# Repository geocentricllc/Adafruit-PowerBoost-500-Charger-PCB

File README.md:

This design is derived from Adafruit's PowerBoost-500 Charger PCB (See attribution below).  The design removes the breakout headers and changes the
USB female connector to a JST M2 right angle connector.

Adafruit-PowerBoost-500-Charger-PCB
=================================

PCB files for the Adafruit PowerBoost 500 Charger

Pick up one today at 

----> https://www.adafruit.com/product/1944

Adafruit invests time and resources providing this open source design, 
please support Adafruit and open-source hardware by purchasing 
products from Adafruit!

Designed by Adafruit Industries.  
Creative Commons Attribution, Share-Alike license, check license.txt for more information
All text above must be included in any redistribution

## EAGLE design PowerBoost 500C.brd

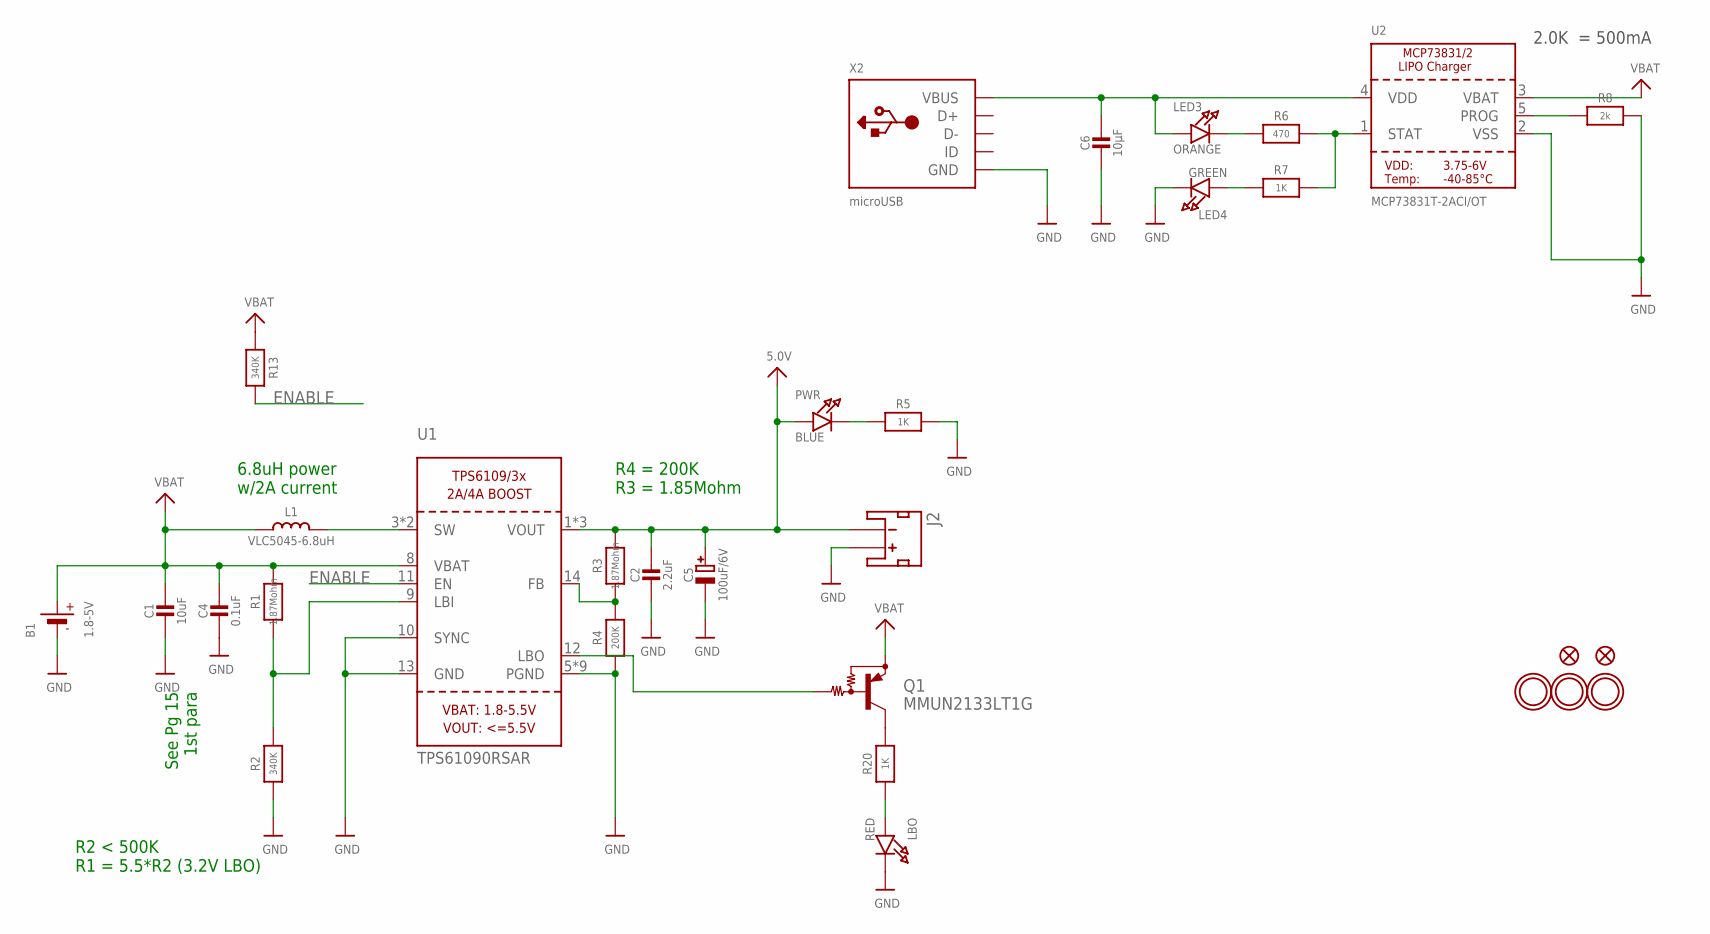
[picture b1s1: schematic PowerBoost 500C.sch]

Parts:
B1: 1.8-5V; JSTPH2
C1: 10uF; 0805-NO
C2: 2.2uF; 0805-NO
C4: 0.1uF; 0805-NO
C5: 100uF/6V; EIA3528-21/B-R
C6: 10µF; 0805-NO
FID2, FID3: FIDUCIAL""; FIDUCIAL_1MM
J2: JST_2MM_MALE; JST-2-SMD
L1: VLC5045-6.8uH; INDUCTOR_5X5MM_TDK_VLC5045
LBO: RED; CHIPLED_0805_NOOUTLINE
LED3: ORANGE; CHIPLED_0805_NOOUTLINE
LED4: GREEN; CHIPLED_0805_NOOUTLINE
PWR: BLUE; CHIPLED_0805_NOOUTLINE
Q1: MMUN2133LT1G; SC59-BEC
R1, R3: 1.87Mohm; 0805-NO
R2, R13: 340K; 0805-NO
R4: 200K; 0805-NO
R5, R7, R20: 1K; 0805-NO
R6: 470; 0805-NO
R8: 2k; 0805-NO
U1: TPS61090RSAR; PVQFN-16
U2: MCP73831T-2ACI/OT; SOT23-5
U$10, U$12, U$15: MOUNTINGHOLE2.5; MOUNTINGHOLE_2.5_PLATED
X2: microUSB; 4UCONN_20329

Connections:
5.0V: C2.1, C5.+, J2.1 (-), PWR.A, R3.2, U1.1 (VOUT), U1.15 (VOUT), U1.16 (VOUT)
ENABLE: R13.2, U1.11 (EN)
GND: B1.1 (-), C1.2, C2.2, C4.2, C5.-, C6.2, J2.2 (+), LBO.C, LED4.C, R2.1, R4.1, R5.2, R8.2, U1.5 (PGND), U1.6 (PGND), U1.7 (PGND), U1.10 (SYNC), U1.13 (GND), U1.P$18 (PGND), U1.P$19 (PGND), U1.P$20 (PGND), U1.P$21 (PGND), U1.P$22 (PGND), U1.THERMAL (PGND), U2.2 (VSS), X2.BASE@1 (GND), X2.BASE@2 (GND), X2.GND, X2.SPRT@1 (GND), X2.SPRT@2 (GND), X2.SPRT@3 (GND), X2.SPRT@4 (GND)
LBO: Q1.B, U1.12 (LBO)
unnamed: L1.P$2 (2), U1.3 (SW), U1.4 (SW)
unnamed: LBO.A, R20.1
unnamed: R1.1, R2.2, U1.9 (LBI)
unnamed: PWR.C, R5.1
unnamed: R3.1, R4.2, U1.14 (FB)
unnamed: LED3.C, R6.1
unnamed: R6.2, R7.2, U2.1 (STAT)
unnamed: R8.1, U2.5 (PROG)
unnamed: LED4.A, R7.1
unnamed: Q1.C, R20.2
VBAT: B1.2 (+), C1.1, C4.1, L1.P$1 (1), Q1.E, R1.2, R13.1, U1.8 (VBAT), U2.3 (VBAT)
VDD1: C6.1, LED3.A, U2.4 (VDD), X2.VBUS

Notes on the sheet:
See Pg 15 1st para
6.8uH power w/2A current
R2 < 500K R1 = 5.5*R2 (3.2V LBO)
R4 = 200K R3 = 1.85Mohm
2.0K = 500mA

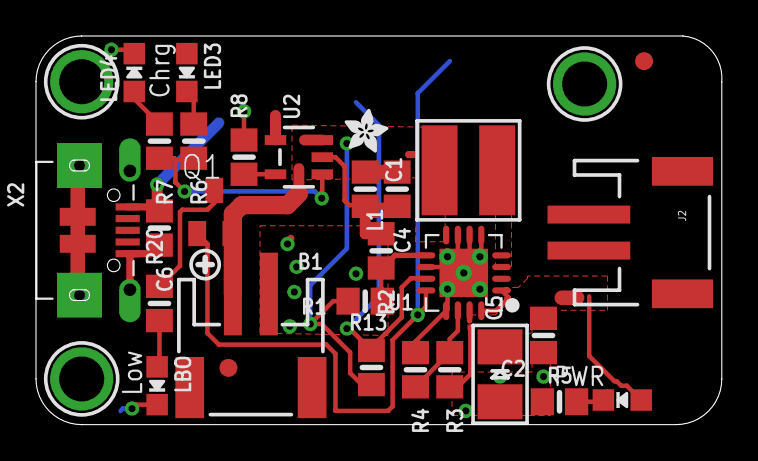
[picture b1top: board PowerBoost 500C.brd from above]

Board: 2 copper layers, 38.1 x 21.6 mm, 34 parts (1 on the bottom side), 16 nets.

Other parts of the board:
U$13: SYMBOL_PLUS
U$28: ADAFRUIT_2.5MM
U$29: ADAFRUIT_5MM

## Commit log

2017-05-31 Update the readme

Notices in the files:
parts and their libraries:
microbuilder: This work is placed in the public domain, and may be freely used for commercial and non-commercial work with the following conditions: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
SparkFun-Connectors: Licensing: Creative Commons ShareAlike 4.0 International - https://creativecommons.org/licenses/by-sa/4.0
